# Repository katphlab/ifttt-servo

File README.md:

# Controlling Servo motor using IFTTT and MQTT
This project uses IFTTT and MQTT to remotely control a Servo motor using ESP8266 only <br>

## Required Software
- [NodeMCU Firmware](https://nodemcu-build.com/), build your own, I chose MQTT and CJOS in addition to defaults, make sure that your firmware size is less than your module flash size. My flash size is 4Mbit, and firmware size is 405KB
- [NodeMCU Flasher](https://github.com/nodemcu/nodemcu-flasher), for flashing the NodeMCU firmware
- [ESPlorer](https://esp8266.ru/esplorer/)

## Required Hardware
- USB-UART converter, an Arduino can be used as well for this purpose
- ESP8266, are available for low cost from amazon or aliexpress
- Servo, I'm using SG90 servo motor
- Jumper wires and a Breadboard for connections<br>

### For layout and setup instructions, refer to sources in credits

# All credits to the following sources<br>
- Controlling servo motor using ESP8266 is explained at [RoboMero](http://www.roboremo.com/esp8266-servo.html)<br>
- Using IFTTT and MQTT is explained in [this](https://www.hackster.io/devicehub-net/do-button-from-ifttt-home-automation-example-494a1a) hackster project
- NodeMCU Team

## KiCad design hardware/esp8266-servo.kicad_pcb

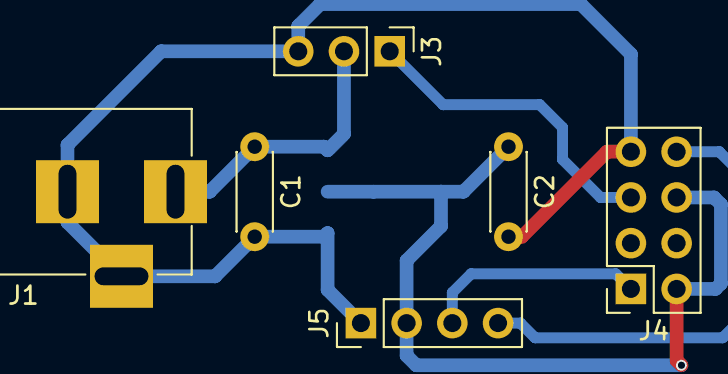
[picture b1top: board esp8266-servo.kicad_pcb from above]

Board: 2 copper layers, 7 parts (1 on the bottom side), 6 nets.

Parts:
C1, C2: 10uF; C_Disc_D4.3mm_W1.9mm_P5.00mm
J1: BARREL_JACK
J3: SERVO; Pin_Header_Straight_1x03_Pitch2.54mm
J4: ESP8266; Socket_Strip_Straight_2x04_Pitch2.54mm
J5: CONN_01X04; Pin_Header_Straight_1x04_Pitch2.54mm
U1: LM1117-3.3; SOT-223

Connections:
+3V3: C2.1, J4.2, J4.6, J5.2, U1.2, U1.4
/RXD: J4.1, J5.3
/SERVO_SIG: J3.1, J4.5
/TXD: J4.8, J5.4
GND: C1.2, C2.2, J1.2, J1.3, J3.3, J4.7, J5.1, U1.1
VDD: C1.1, J1.1, J3.2, U1.3

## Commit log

2017-04-14 Add Lua codes
2017-04-14 Add kicad files
2017-11-25 Final commit
